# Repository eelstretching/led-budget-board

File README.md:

# led-budget-board

A "budget" LED processor board: a carrier for a Raspberry Pi Pico 2 W that drives 16 strands
through two of the standard 16-pin output shrouds. Little sibling of
[led-processor-board](https://github.com/eelstretching/led-processor-board).

## What it is

| | led-processor-board | led-budget-board |
|---|---|---|
| Brain | RP2350B, flash, PSRAM and RM2 radio on the board | A Pico 2 W in two 1x20 sockets |
| Outputs | 4 shrouds, 32 strands, GPIO0-31 | 2 shrouds, 16 strands: OUT1 = GP0-7, OUT2 = GP8-15 |
| RTC | DS3231 and coin cell | None: time comes from the show leader's PicoComm beacons |
| USB, BOOTSEL, LED, SWD | On the board | The Pico's own |
| Debug UART | UART1 on GPIO36/37 | UART0 on GP16 (TX) / GP17 (RX), header J4 |
| I2C | (v1.1) I2C0 on GPIO32/33 | I2C0 on GP20 (SDA) / GP21 (SCL), 10k pull-ups: pin header J5 and STEMMA QT / Qwiic socket J7 |
| Spare I/O | GPIO35-42 | GP18, GP19, GP22, GP26-28 on header J6 |
| 3.3 V | NCP1117 on the board | The Pico's 3V3 pin |

The same on both boards:

- Shroud pinout: data 1-8 on even pins 2-16, GND on odd pins 1-11, pin 13 = 3.3 V, pin 15 = 5 V.
  Pin 1 is the triangle on the shroud. 33R in series with each data line, 100 nF on each rail.
- Power: 12 V barrier terminal (the output boards' DBT50G-9.5-2P, takes 14 AWG), SS34 against a reversed lead, TPS54202H 5 V buck (same parts and
  values), then a B5819W into the Pico's VSYS so USB and 12 V can be plugged in together.
- RUN button and a 5 V power LED.

## Files

- `led-budget-board.kicad_sch`: the schematic (KiCad 10), one A3 sheet. PDF in `docs/schematic.pdf`.
- `led-budget-board.kicad_sym`: the Pico 2 W symbol (the stock Pico W symbol with AGND made passive and
  the through-hole footprint).
- `tools/build_schematic.py`: wrote the first version of the schematic. Edit the schematic in KiCad from
  now on; re-running the script overwrites it.
- `led-budget-board.kicad_pcb`: the board, 61.5 x 73 mm, two layers, fully routed. The design rules check
  is clean (no errors, no warnings, nothing unconnected, matches the schematic).
- `tools/pcb/build_pcb.py`: placed and routed the board. Same warning: it overwrites the board.

## Layout

- Pico 2 W upright with USB at the top edge. Both shrouds on the right edge, pin 1 at the top, key notch
  facing into the board: an output board sitting to the right with its shroud edge towards this board
  gets a straight ribbon with no twist.
- Data lines: Pico pin, 33R, via, straight across under the Pico on the bottom layer, then between the
  shroud's ground pins to the even pin. GP13-15 go round the Pico W antenna keep-out.
- The 5 V buck is the processor board's layout, copied part for part and track for track.
- Down the left side: the buck, D1, then J1. J1's wire entry faces the left edge, the whole housing
  sits on the board, +12V is the top screw. The STEMMA QT socket is below it on the same edge.
- The logo and the board name are under the Pico, between its pin rows.
- The Pico's right-hand pins run down the gap between the Pico and the shrouds to the headers on the
  bottom edge. J6 (spare) is GND, GP18, GP19, GP22, GP26, GP27, GP28, 3V3, left to right.
- J5 (I2C header, bottom right) and J7 (STEMMA QT, left edge) share the bus and the 10k pull-ups.

## Ordering from JLCPCB

`production/` holds the upload set for full assembly (SMD and through-hole), made by `tools/jlc.py`:

- `led-budget-board-gerbers.zip`: gerbers and drill files.
- `jlcpcb-bom.csv` and `jlcpcb-cpl.csv`: the parts list and placement file, 24 lines, 49 parts
  (41 SMD, 8 through-hole).
- `bom-full.csv`: the same list for people, plus what JLC does not fit.

The Pico 2 W is not on the list. JLC fits two 1x20 sockets in its place (A1A and A1B in the files) and
the Pico plugs in afterwards. Check in JLC's placement preview that every part sits the right way round,
the through-hole ones especially; `ROT_FIX` in `tools/jlc.py` is where a correction goes.

## Firmware

`firmware/boards/led_budget_board.h` is the pico-sdk board header. It is `pico2_w.h` with the default
UART moved to UART0 on GP16 (TX) / GP17 (RX) and the default I2C to I2C0 on GP20 (SDA) / GP21 (SCL),
and it defines `LED_BUDGET_BOARD` for code that needs to tell the boards apart, plus the output pin
numbers (`LED_BUDGET_BOARD_OUT1_FIRST_PIN` = 0, `..._OUT2_FIRST_PIN` = 8). Use it with:

    set(PICO_BOARD led_budget_board)
    set(PICO_BOARD_HEADER_DIRS <path to led-budget-board>/firmware/boards)

both before `pico_sdk_init()` / `project()`; or `-DPICO_BOARD=led_budget_board
-DPICO_BOARD_HEADER_DIRS=<absolute path>`. Firmware should still turn on USB stdio itself
(`pico_enable_stdio_usb`), since that is a per-target setting. The header's macros were checked with the C
preprocessor against pico-sdk 2.3.0's `pico2_w.h`; it has not been built into a firmware image yet.

## Still to do

- Build a PicoLEDs example for `led_budget_board` once the boards arrive (about 10-12 days), and check
  both outputs on the bench.

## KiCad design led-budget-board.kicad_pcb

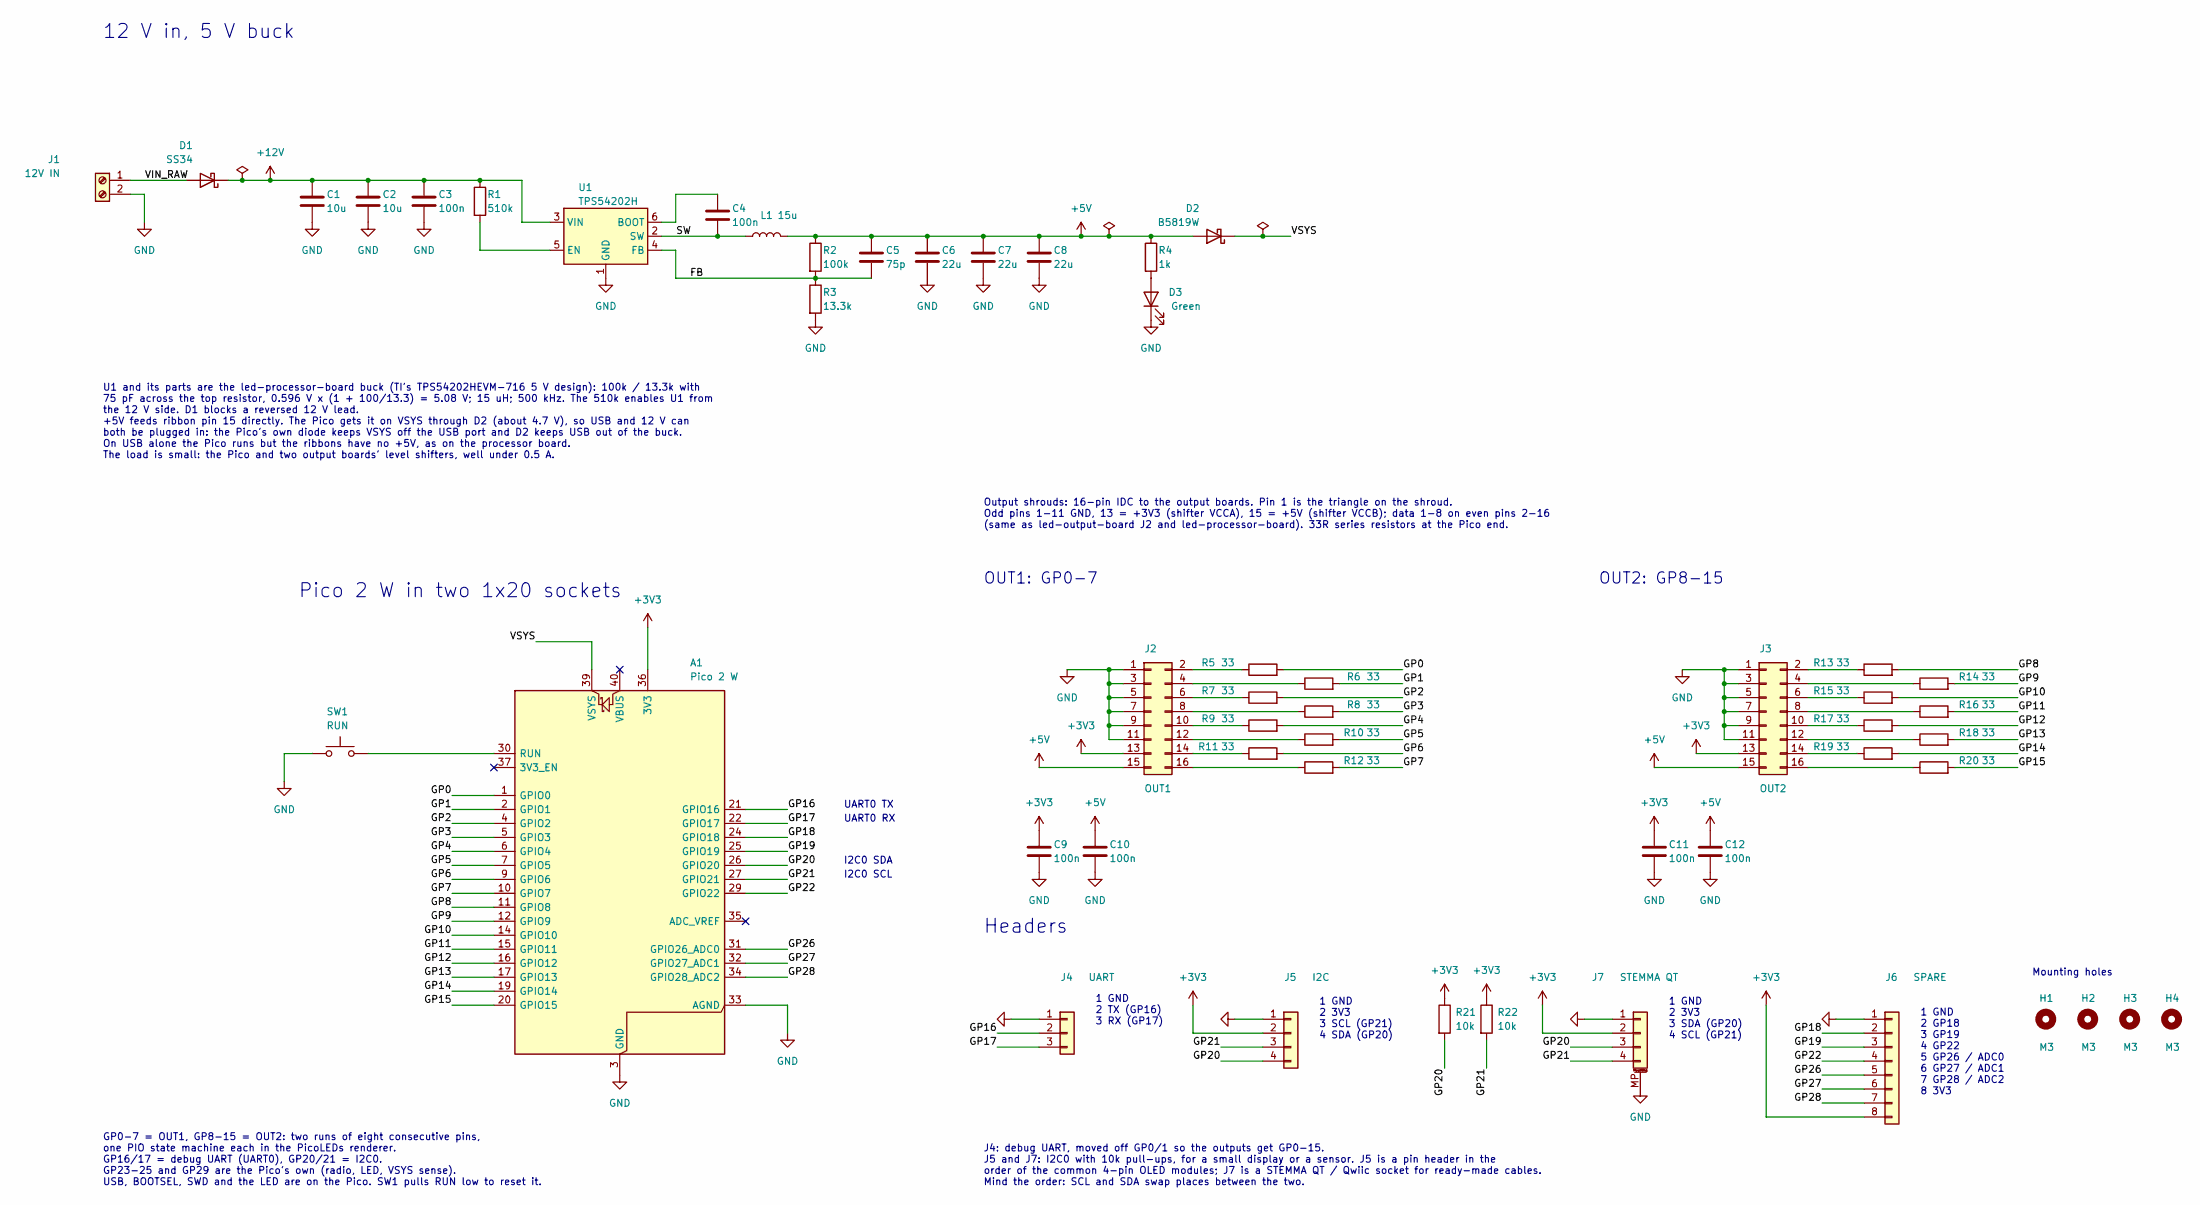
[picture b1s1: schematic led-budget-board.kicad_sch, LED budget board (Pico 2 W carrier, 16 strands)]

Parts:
A1: Pico 2 W; RaspberryPi_Pico_Common_THT; manufacturer_pn SC1633
C1, C2: 10u; C_0805_2012Metric; manufacturer_pn CL21A106KBYNNNE; LCSC C440198
C3, C4: 100n; C_0603_1608Metric; manufacturer_pn CC0603KRX7R9BB104; LCSC C14663
C5: 75p; C_0402_1005Metric; manufacturer_pn 0402CG750J500NT; LCSC C37809
C6, C7, C8: 22u; C_0805_2012Metric; manufacturer_pn CL21A226MAQNNNE; LCSC C45783
C9, C10, C11, C12: 100n; C_0402_1005Metric; manufacturer_pn CL05B104KO5NNNC; LCSC C1525
D1: SS34; D_SMA; manufacturer_pn SS34; LCSC C8678
D2: B5819W; D_SOD-123; manufacturer_pn B5819W SL; LCSC C8598
D3: Green; LED_0603_1608Metric; manufacturer_pn KT-0603YG; LCSC C2289
H1, H2, H3, H4: M3; MountingHole_3.2mm_M3
J1: 12V IN; CONN-TH_2P-P9.50_DBT50G-9.5-2P; manufacturer_pn DBT50G-9.5-2P; LCSC C395958
J2: OUT1; IDC-Header_2x08_P2.54mm_Vertical; manufacturer_pn 2.54-2*8P; LCSC C3406
J3: OUT2; IDC-Header_2x08_P2.54mm_Vertical; manufacturer_pn 2.54-2*8P; LCSC C3406
J4: UART; PinHeader_1x03_P2.54mm_Vertical; manufacturer_pn 2.54-1*3P; LCSC C49257
J5: I2C; PinHeader_1x04_P2.54mm_Vertical; manufacturer_pn B-2100S04P-A110; LCSC C124378
J6: SPARE; PinHeader_1x08_P2.54mm_Vertical; manufacturer_pn B-2100S08P-A110; LCSC C124381
J7: STEMMA QT; JST_SH_SM04B-SRSS-TB_1x04-1MP_P1.00mm_Horizontal; manufacturer_pn SM04B-SRSS-TB(LF)(SN); LCSC C160404
L1: 15u; L_Sunlord_SWPA8040S; manufacturer_pn SWPA8040S150MT; LCSC C16853
R1: 510k; R_0402_1005Metric; manufacturer_pn 0402WGF5103TCE; LCSC C11616
R2: 100k; R_0402_1005Metric; manufacturer_pn 0402WGF1003TCE; LCSC C25741
R3: 13.3k; R_0402_1005Metric; manufacturer_pn 0402WGF1332TCE; LCSC C122547
R4: 1k; R_0402_1005Metric; manufacturer_pn 0402WGF1001TCE; LCSC C11702
R5, R6, R7, R8, R9, R10, R11, R12, R13, R14, R15, R16, R17, R18, R19, R20: 33; R_0402_1005Metric; manufacturer_pn 0402WGF330JTCE; LCSC C25105
R21, R22: 10k; R_0402_1005Metric; manufacturer_pn 0402WGF1002TCE; LCSC C25744
SW1: RUN; SW_SPST_TS-1088-xR025; manufacturer_pn TS-1088R-02526; LCSC C455281
U1: TPS54202H; SOT-23-6; manufacturer_pn TPS54202HDDCR; LCSC C527684

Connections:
+3V3: A1.36 (3V3), C9.1, C11.1, J2.13, J3.13, J5.2, J6.8, J7.2, R21.1, R22.1
+5V: C5.1, C6.1, C7.1, C8.1, C10.1, C12.1, D2.2 (A), J2.15, J3.15, L1.2, R2.1, R4.1
+12V: C1.1, C2.1, C3.1, D1.1 (K), R1.1, U1.3 (VIN)
/FB: C5.2, R2.2, R3.1, U1.4 (FB)
/GP0: A1.1 (GPIO0), R5.2
/GP1: A1.2 (GPIO1), R6.2
/GP2: A1.4 (GPIO2), R7.2
/GP3: A1.5 (GPIO3), R8.2
/GP4: A1.6 (GPIO4), R9.2
/GP5: A1.7 (GPIO5), R10.2
/GP6: A1.9 (GPIO6), R11.2
/GP7: A1.10 (GPIO7), R12.2
/GP8: A1.11 (GPIO8), R13.2
/GP9: A1.12 (GPIO9), R14.2
/GP10: A1.14 (GPIO10), R15.2
/GP11: A1.15 (GPIO11), R16.2
/GP12: A1.16 (GPIO12), R17.2
/GP13: A1.17 (GPIO13), R18.2
/GP14: A1.19 (GPIO14), R19.2
/GP15: A1.20 (GPIO15), R20.2
/GP16: A1.21 (GPIO16), J4.2
/GP17: A1.22 (GPIO17), J4.3
/GP18: A1.24 (GPIO18), J6.2
/GP19: A1.25 (GPIO19), J6.3
/GP20: A1.26 (GPIO20), J5.4, J7.3, R21.2
/GP21: A1.27 (GPIO21), J5.3, J7.4, R22.2
/GP22: A1.29 (GPIO22), J6.4
/GP26: A1.31 (GPIO26_ADC0), J6.5
/GP27: A1.32 (GPIO27_ADC1), J6.6
/GP28: A1.34 (GPIO28_ADC2), J6.7
/SW: C4.2, L1.1, U1.2 (SW)
/VIN_RAW: D1.2 (A), J1.1
/VSYS: A1.39 (VSYS), D2.1 (K)
GND: A1.3 (GND), A1.8 (GND), A1.13 (GND), A1.18 (GND), A1.23 (GND), A1.28 (GND), A1.33 (AGND), A1.38 (GND), C1.2, C2.2, C3.2, C6.2, C7.2, C8.2, C9.2, C10.2, C11.2, C12.2, D3.1 (K), J1.2, J2.1, J2.3, J2.5, J2.7, J2.9, J2.11, J3.1, J3.3, J3.5, J3.7, J3.9, J3.11, J4.1, J5.1, J6.1, J7.1, J7.MP (MountPin), R3.2, SW1.1, U1.1 (GND)
unnamed: A1.30 (RUN), SW1.2
unnamed: D3.2 (A), R4.2
unnamed: J2.2, R5.1
unnamed: J2.4, R6.1
unnamed: J2.6, R7.1
unnamed: J2.8, R8.1
unnamed: J2.10, R9.1
unnamed: J2.12, R10.1
unnamed: J2.14, R11.1
unnamed: J2.16, R12.1
unnamed: J3.2, R13.1
unnamed: J3.4, R14.1
unnamed: J3.6, R15.1
unnamed: J3.8, R16.1
unnamed: J3.10, R17.1
unnamed: J3.12, R18.1
unnamed: J3.14, R19.1
unnamed: J3.16, R20.1
unnamed: C4.1, U1.6 (BOOT)
unnamed: R1.2, U1.5 (EN)

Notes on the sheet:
12 V in, 5 V buck
U1 and its parts are the led-processor-board buck (TI's TPS54202HEVM-716 5 V design): 100k / 13.3k with 75 pF across the top resistor, 0.596 V x (1 + 100/13.3) = 5.08 V; 15 uH; 500 kHz. The 510k enables U1 from the 12 V side. D1 blocks a reversed 12 V lead. +5V feeds ribbon pin 15 directly. The Pic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
Pico 2 W in two 1x20 sockets
UART0 TX
UART0 RX
I2C0 SDA
I2C0 SCL
GP0-7 = OUT1, GP8-15 = OUT2: two runs of eight consecutive pins, one PIO state machine each in the PicoLEDs renderer. GP16/17 = debug UART (UART0), GP20/21 = I2C0. GP23-25 and GP29 are the Pico's own (radio, LED, VSYS sense). USB, BOOTSEL, SWD and the LED are on the Pico. SW1 pulls RUN low to reset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
Output shrouds: 16-pin IDC to the output boards. Pin 1 is the triangle on the shroud. Odd pins 1-11 GND, 13 = +3V3 (shifter VCCA), 15 = +5V (shifter VCCB); data 1-8 on even pins 2-16 (same as led-output-board J2 and led-processor-board). 33R series resistors at the Pico end.
OUT1: GP0-7
OUT2: GP8-15
Headers
1 GND 2 TX (GP16) 3 RX (GP17)
1 GND 2 3V3 3 SCL (GP21) 4 SDA (GP20)
1 GND 2 3V3 3 SDA (GP20) 4 SCL (GP21)
1 GND 2 GP18 3 GP19 4 GP22 5 GP26 / ADC0 6 GP27 / ADC1 7 GP28 / ADC2 8 3V3
J4: debug UART, moved off GP0/1 so the outputs get GP0-15. J5 and J7: I2C0 with 10k pull-ups, for a small display or a sensor. J5 is a pin header in the order of the common 4-pin OLED modules; J7 is a STEMMA QT / Qwiic socket for ready-made cables. Mind the order: SCL and SDA swap places between th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
Mounting holes

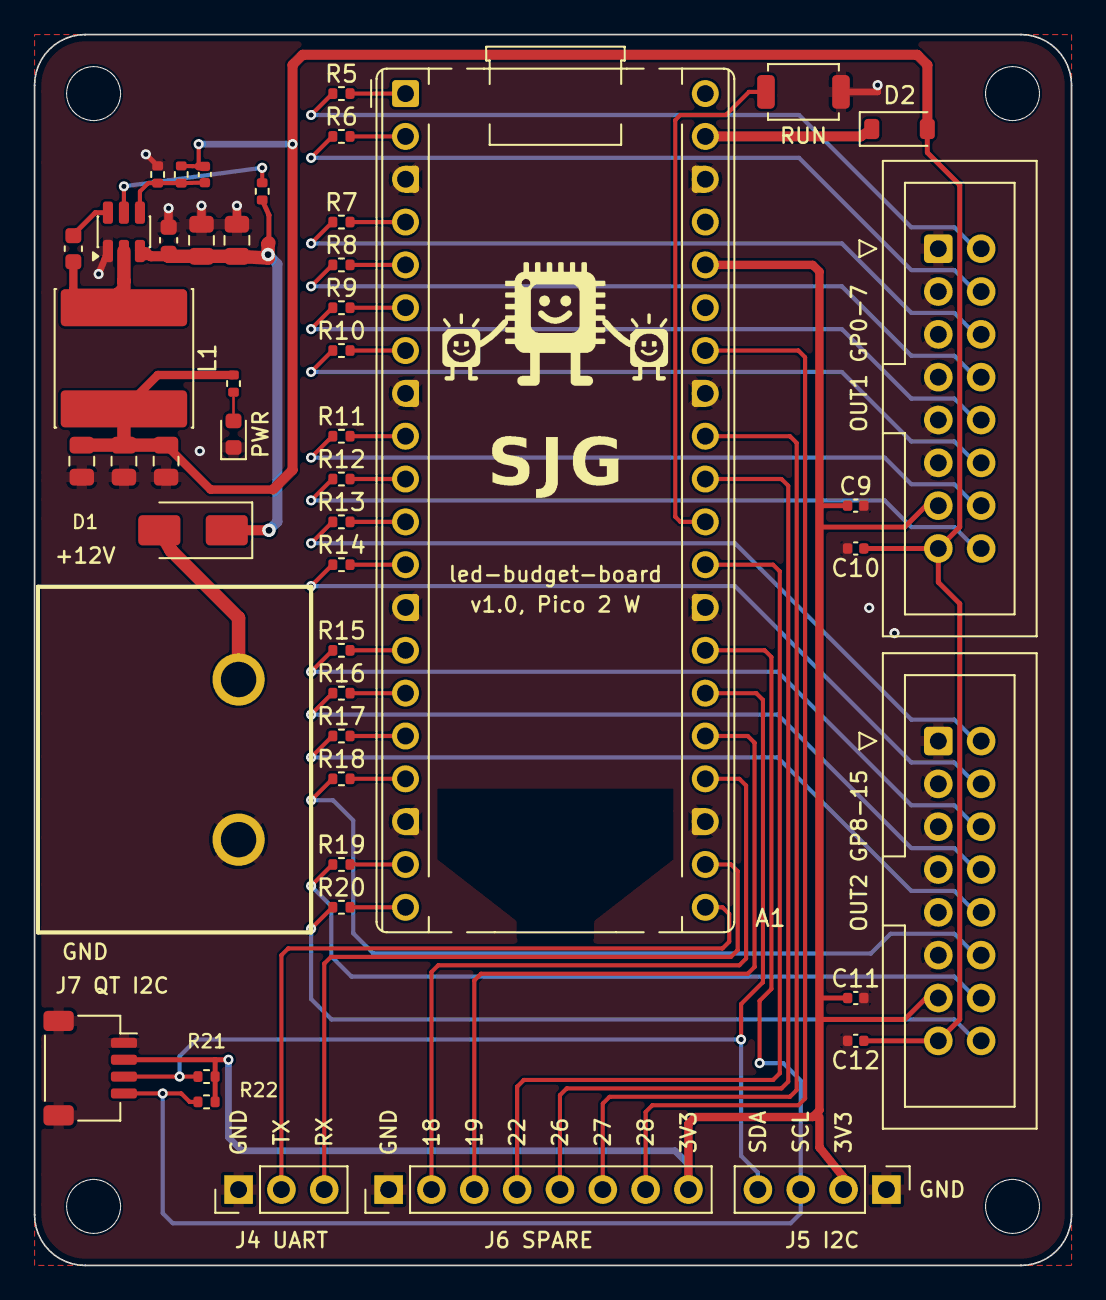
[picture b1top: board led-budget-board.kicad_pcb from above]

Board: 2 copper layers, 61.5 x 73.0 mm, 53 parts (0 on the bottom side), 54 nets.

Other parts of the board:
G1: SJG_BigBrother

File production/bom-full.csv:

Comment,Designator,Footprint,LCSC,Manufacturer PN,Qty,Note
2.54-1*20P female header,"A1A,A1B",PinSocket_1x20_P2.54mm_Vertical,C50984,BOOMELE 2.54-1*20P,2,Through-hole
10u,"C1,C2",C_0805_2012Metric,C440198,CL21A106KBYNNNE,2,
100n,"C3,C4",C_0603_1608Metric,C14663,CC0603KRX7R9BB104,2,
75p,C5,C_0402_1005Metric,C37809,0402CG750J500NT,1,
22u,"C6,C7,C8",C_0805_2012Metric,C45783,CL21A226MAQNNNE,3,
100n,"C9,C10,C11,C12",C_0402_1005Metric,C1525,CL05B104KO5NNNC,4,
SS34,D1,D_SMA,C8678,SS34,1,
B5819W,D2,D_SOD-123,C8598,B5819W SL,1,
Green,D3,LED_0603_1608Metric,C2289,KT-0603YG,1,
12V IN,J1,CONN-TH_2P-P9.50_DBT50G-9.5-2P,C395958,DBT50G-9.5-2P,1,Through-hole
OUT1,"J2,J3",IDC-Header_2x08_P2.54mm_Vertical,C3406,2.54-2*8P,2,Through-hole
UART,J4,PinHeader_1x03_P2.54mm_Vertical,C49257,2.54-1*3P,1,Through-hole
I2C,J5,PinHeader_1x04_P2.54mm_Vertical,C124378,B-2100S04P-A110,1,Through-hole
SPARE,J6,PinHeader_1x08_P2.54mm_Vertical,C124381,B-2100S08P-A110,1,Through-hole
STEMMA QT,J7,JST_SH_SM04B-SRSS-TB_1x04-1MP_P1.00mm_Horizontal,C160404,SM04B-SRSS-TB(LF)(SN),1,
15u,L1,L_Sunlord_SWPA8040S,C16853,SWPA8040S150MT,1,
510k,R1,R_0402_1005Metric,C11616,0402WGF5103TCE,1,
100k,R2,R_0402_1005Metric,C25741,0402WGF1003TCE,1,
13.3k,R3,R_0402_1005Metric,C122547,0402WGF1332TCE,1,
1k,R4,R_0402_1005Metric,C11702,0402WGF1001TCE,1,
33,"R5,R6,R7,R8,R9,R10,R11,R12,R13,R14,R15,R16,R17,R18,R19,R20",R_0402_1005Metric,C25105,0402WGF330JTCE,16,
10k,"R21,R22",R_0402_1005Metric,C25744,0402WGF1002TCE,2,
RUN,SW1,SW_SPST_TS-1088-xR025,C455281,TS-1088R-02526,1,
TPS54202H,U1,SOT-23-6,C527684,TPS54202HDDCR,1,
Pico 2 W,A1,RaspberryPi_Pico_Common_THT,,SC1633,1,"Not fitted by JLC: Raspberry Pi Pico 2 W (SC1633): yours, plugs into sockets A1A and A1B"
M3,H1,MountingHole_3.2mm_M3,,,1,Not fitted by JLC: M3 mounting hole
M3,H2,MountingHole_3.2mm_M3,,,1,Not fitted by JLC: M3 mounting hole
M3,H3,MountingHole_3.2mm_M3,,,1,Not fitted by JLC: M3 mounting hole
M3,H4,MountingHole_3.2mm_M3,,,1,Not fitted by JLC: M3 mounting hole
